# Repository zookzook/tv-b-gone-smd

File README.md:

# tv-b-gone-smd
The TV B Gone circuit as smd version and using the Arduino IDE for compiling

Ken Shirriff ported the original code of the tv-b-gone for using the Ardunio and the Ardunio IDE.

https://github.com/shirriff/Arduino-TV-B-Gone

I ported this version back for using an Attiny85 and the Arduino IDE for my TV-B-Gone-Clone. 

This is an SMD version of the well known TV-B-Gone circuit. I have modified the software 
for the Attiny85, so that these are compiled with the Arduino IDE. A macro defines whether US or EU 
codes are used. This releases a PIN for other things.

First you have to set the FUSE-Bits for the Attiny85 with a programmer (for example, with an Ardunio itself).
This requires a ceramic resonator with 8Mhz. In the Ardunio IDE you call
"burn bootloader", but only FUSE bits are set in case of an Attiny85. Then the program can be 
transmitted to the chip as usual. If you don't attach the ceramic resonator it is not possible 
to program the Attiny85 any more.

The result looks like this. It is very small! Now I looking for a nice housing.

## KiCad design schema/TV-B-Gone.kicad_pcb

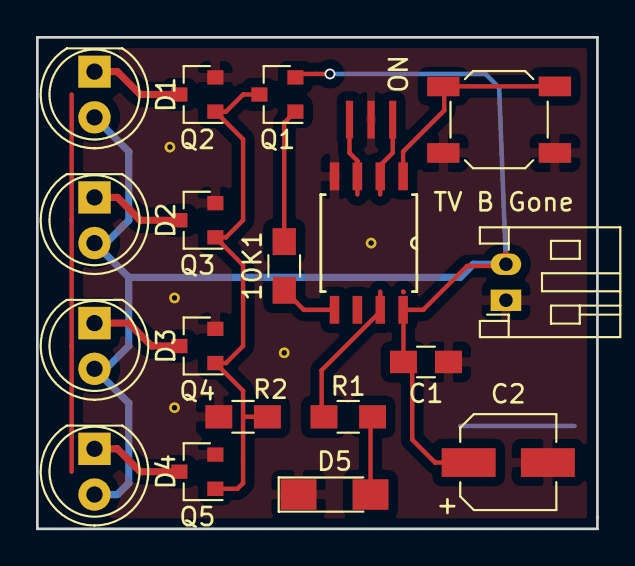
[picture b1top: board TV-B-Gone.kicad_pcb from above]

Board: 2 copper layers, 31.1 x 27.3 mm, 19 parts (0 on the bottom side), 14 nets.

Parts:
10K1: R; R_0805_HandSoldering
C1: C; C_0805_HandSoldering
C2: CP; CP_Elec_5x5.3
D1, D2, D3, D4: LD271; LED_D5.0mm
D5: LED; LED_1206_HandSoldering
J1: Conn_01x02; JST_PH_S2B-PH-K_02x2.00mm_Angled
ON: SW_Push; SW_SPST_SKQG
Q1: MMBT3906; SOT-23
Q2, Q3, Q4, Q5: MMBT3904; SOT-23
R1: 220; R_0805_HandSoldering
R2: R; R_0805_HandSoldering
U1: ATTINY85@8MHz; SOIC127P798X216-8N
Y1: 8MHz; CSTCE8M00G55-R0

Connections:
+BATT: C1.2, C2.1, D1.2, D2.2, D3.2, D4.2, J1.2, Q1.2, U1.8
GND: C1.1, C2.2, D5.1, J1.1, ON.2, Q2.2, Q3.2, Q4.2, Q5.2, R2.1, U1.4, Y1.2
unnamed: 10K1.1, Q1.1
unnamed: 10K1.2, U1.5
unnamed: Q1.3, Q2.1, Q3.1, Q4.1, Q5.1, R2.2
unnamed: D1.1, Q2.3
unnamed: D2.1, Q3.3
unnamed: D3.1, Q4.3
unnamed: D4.1, Q5.3
unnamed: D5.2, R1.2
unnamed: R1.1, U1.7
unnamed: ON.1, U1.1
unnamed: U1.2, Y1.1
unnamed: U1.3, Y1.3

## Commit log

2018-01-02 Initial version
2018-01-02 Linked mod-file added, images of circuit and schema added
2018-01-02 Edited readme
2018-01-02 added new image
